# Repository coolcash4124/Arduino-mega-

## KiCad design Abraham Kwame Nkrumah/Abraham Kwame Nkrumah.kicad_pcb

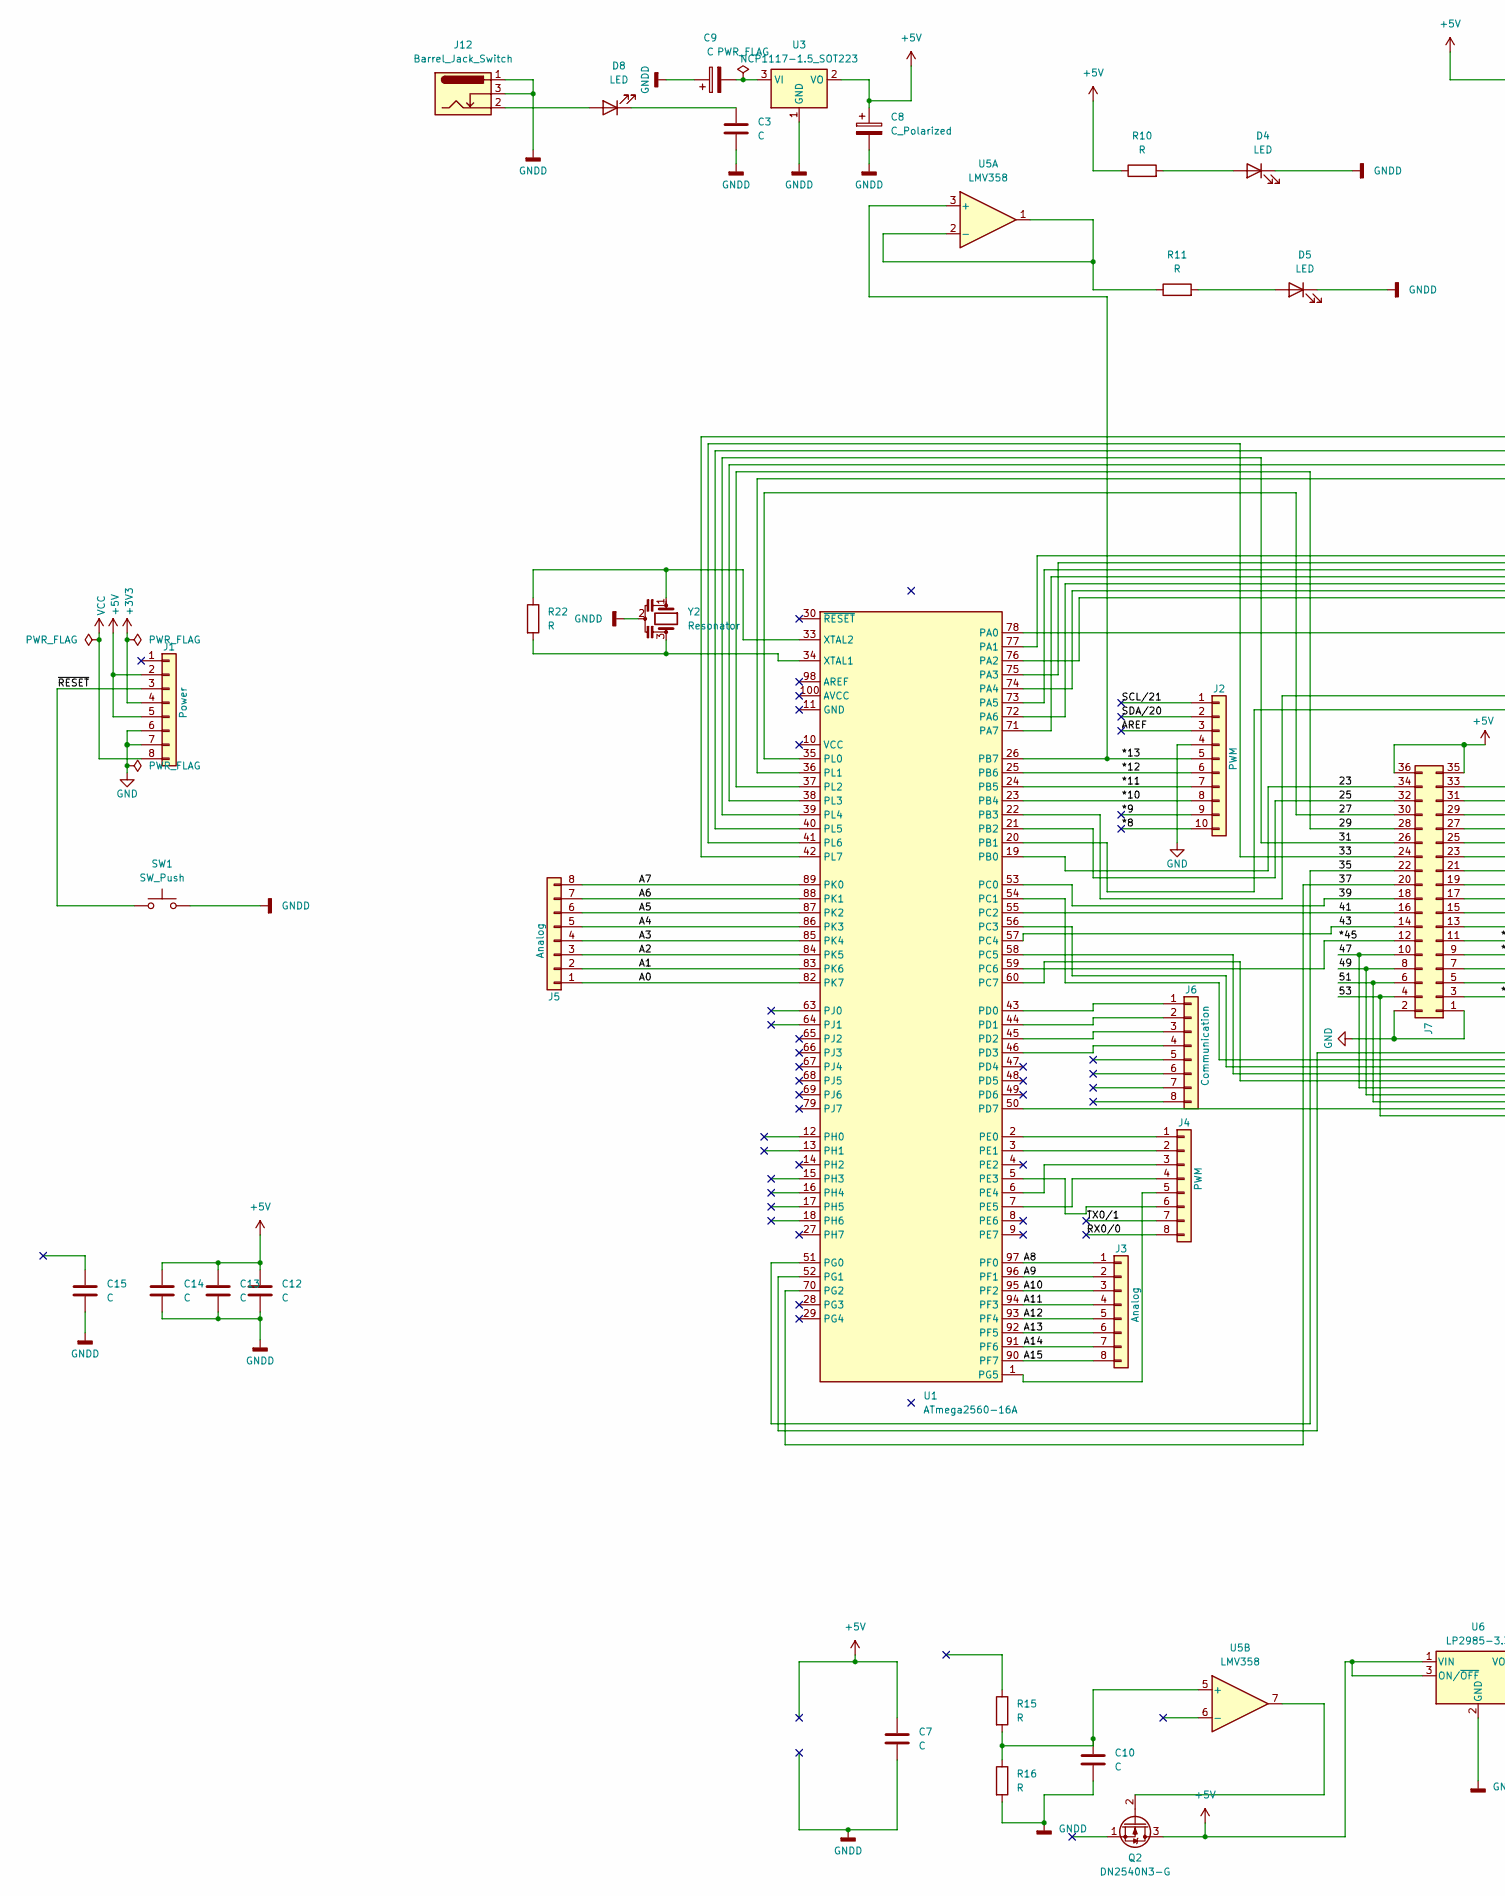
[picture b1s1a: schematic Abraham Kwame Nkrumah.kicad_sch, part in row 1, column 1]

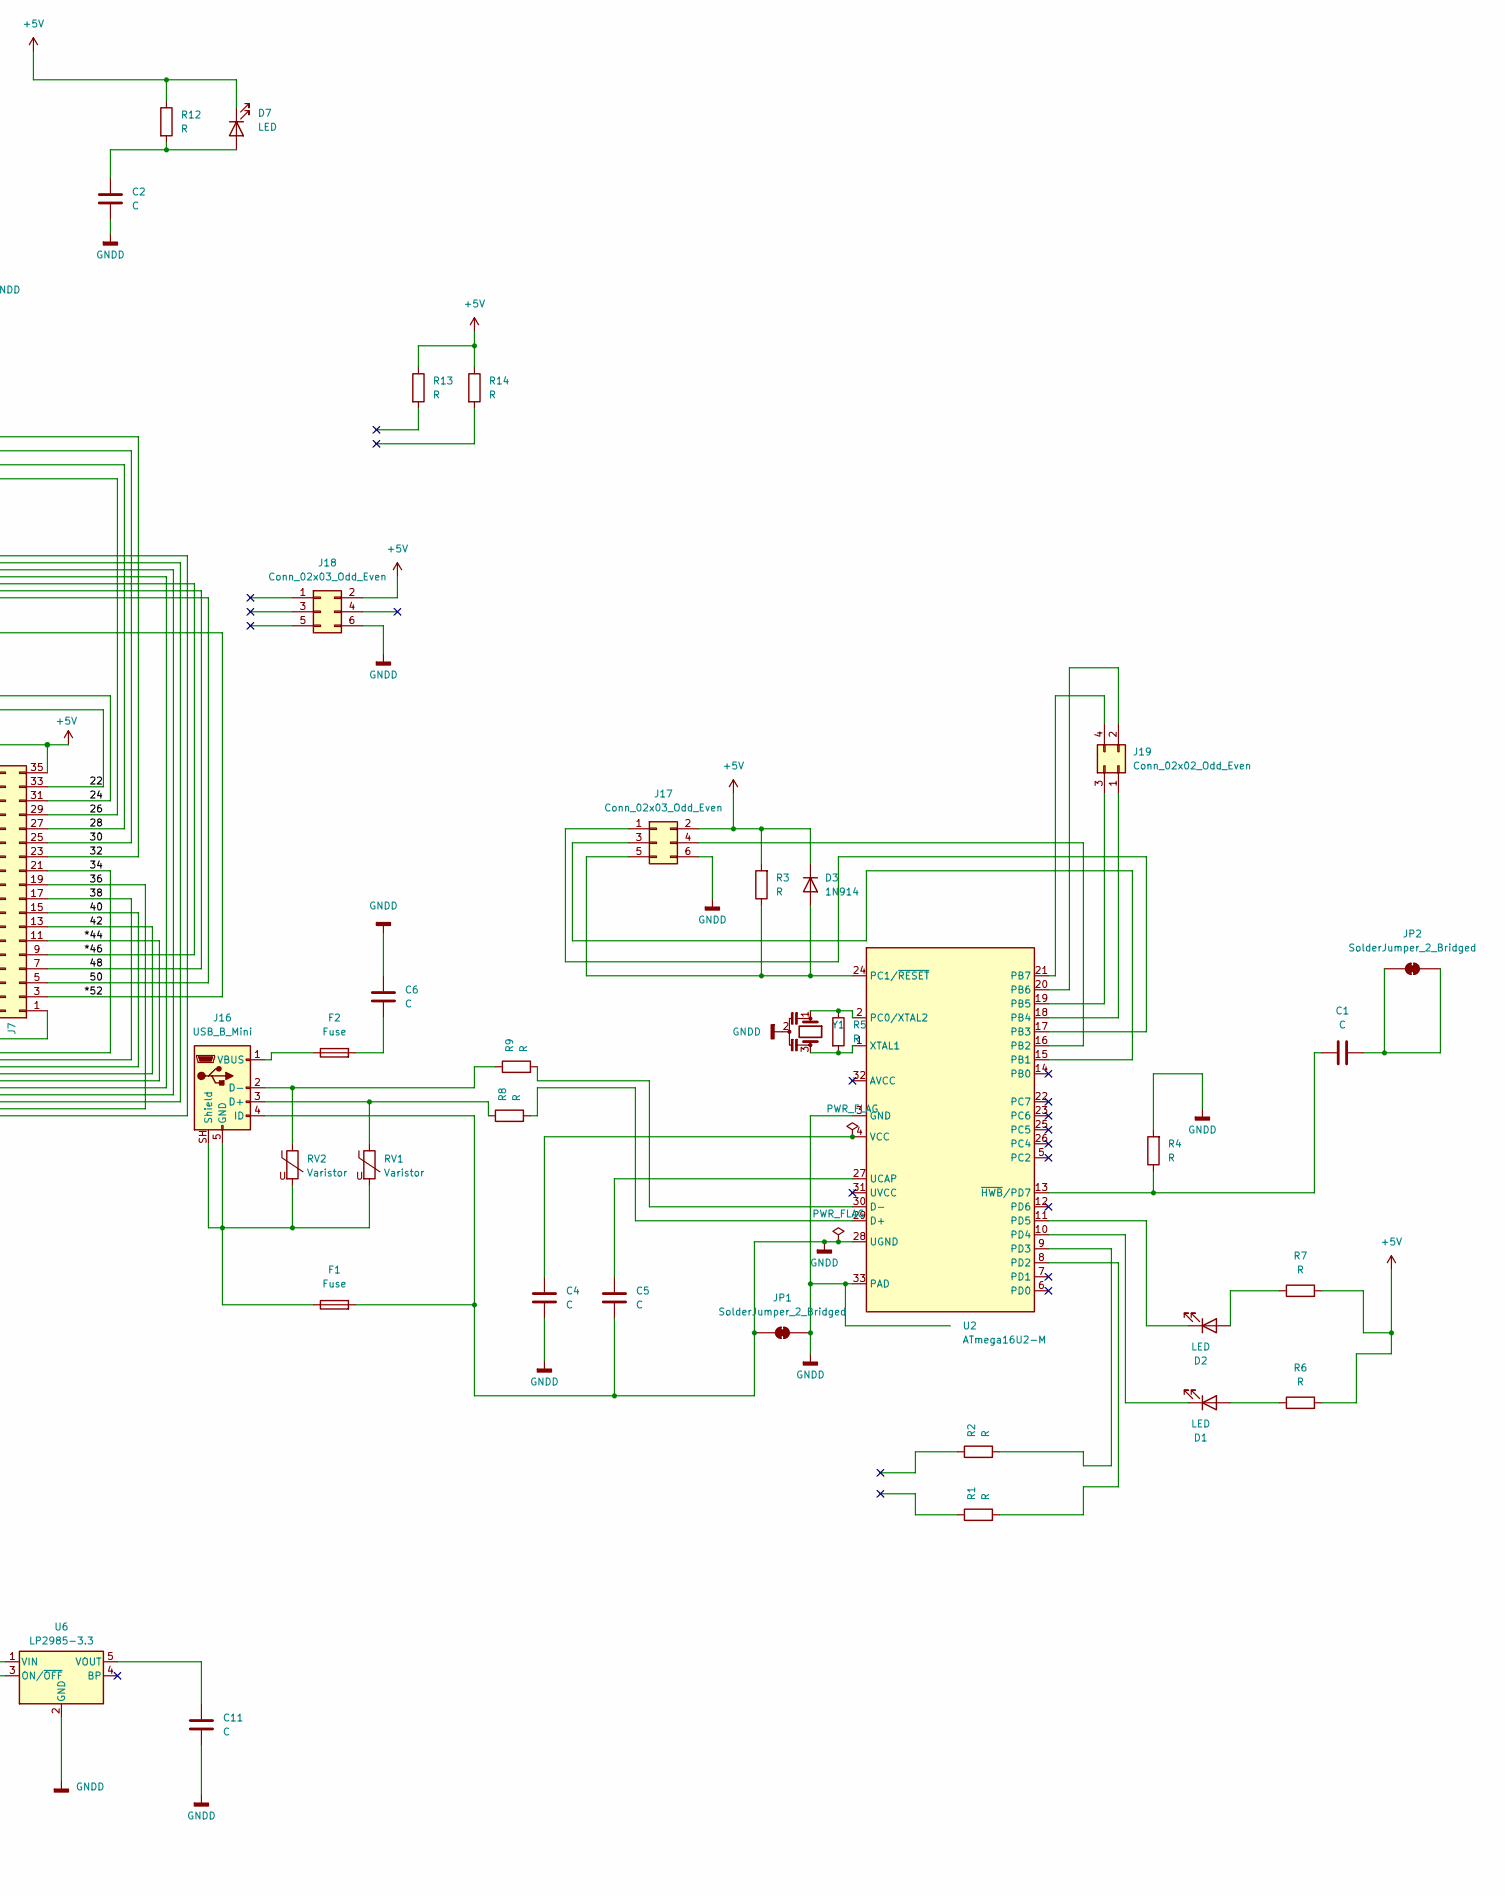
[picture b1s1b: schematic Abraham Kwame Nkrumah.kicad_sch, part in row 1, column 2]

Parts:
C1, C2, C3, C4, C5, C6, C11, C12, C13, C14, C15: C; C_0201_0603Metric_Pad0.64x0.40mm_HandSolder
C7: C; R_0201_0603Metric_Pad0.64x0.40mm_HandSolder
C8: C_Polarized; CP_Elec_4x3
C9: C; CP_Elec_4x3
C10: C; C_Disc_D3.0mm_W2.0mm_P2.50mm
D1, D2: LED; LED_0402_1005Metric
D3: 1N914; Diode_Bridge_DIP-4_W5.08mm_P2.54mm
D4, D5, D7, D8: LED; LED_0201_0603Metric
F1, F2: Fuse; Fuse_0603_1608Metric
J1: Power; PinSocket_1x08_P2.54mm_Vertical
J2: PWM; PinSocket_1x10_P2.54mm_Vertical
J3, J5: Analog; PinSocket_1x08_P2.54mm_Vertical
J4: PWM; PinSocket_1x08_P2.54mm_Vertical
J6: Communication; PinSocket_1x08_P2.54mm_Vertical
J7: Digital; PinSocket_2x18_P2.54mm_Vertical
J12: Barrel_Jack_Switch; BarrelJack_GCT_DCJ200-10-A_Horizontal
J16: USB_B_Mini; USB_B_Lumberg_2411_02_Horizontal
J17, J18: Conn_02x03_Odd_Even; PinSocket_2x03_P1.27mm_Vertical
J19: Conn_02x02_Odd_Even; Samtec_HLE-102-02-xxx-DV-BE-LC_2x02_P2.54mm_Horizontal
JP1, JP2: SolderJumper_2_Bridged; SolderJumper-2_P1.3mm_Bridged_RoundedPad1.0x1.5mm
Q2: DN2540N3-G; TO-92Flat
R1, R2, R3, R4, R5, R6, R7, R8, R9, R10, R13, R14, R15, R16, R22: R; R_0201_0603Metric_Pad0.64x0.40mm_HandSolder
R11: R; R_01005_0402Metric_Pad0.57x0.30mm_HandSolder
R12: R; R_0201_0603Metric
RV1: Varistor; RV_Disc_D12mm_W4mm_P7.5mm
RV2: Varistor; RV_Disc_D7mm_W3.5mm_P5mm
SW1: SW_Push; SW_PUSH_6mm_H5mm
U1: ATmega2560-16A; TQFP-100_14x14mm_P0.5mm
U2: ATmega16U2-M; QFN-32-1EP_5x5mm_P0.5mm_EP3.45x3.45mm
U3: NCP1117-1.5_SOT223; SOT-223-3_TabPin2
U5: LMV358; VSSOP-8_3x3mm_P0.65mm
U6: LP2985-3.3; SOT-23-5
Y1: Resonator; Resonator_Murata_DSS6-3Pin_W7.0mm_H2.5mm
Y2: Resonator; Resonator_Murata_CSTLSxxxG-3Pin_W8.0mm_H3.0mm

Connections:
+3V3: J1.4
+5V: C7.1, C8.1, C12.1, C13.1, C14.1, D3.1 (K), D7.1 (K), J1.2, J1.5, J7.35, J7.36, J17.2, J18.2, Q2.3 (D), R3.2, R6.2, R7.2, R10.1, R12.1, R13.1, R14.1, U3.2 (VO), U6.1 (VIN), U6.3 (ON/~OFF)
/22: J7.33, U1.20 (PB1)
/23: J7.34, U1.19 (PB0)
/24: J7.31, U1.22 (PB3)
/25: J7.32, U1.21 (PB2)
/26: J7.29, U1.36 (PL1)
/27: J7.30, U1.35 (PL0)
/28: J7.27, U1.38 (PL3)
/29: J7.28, U1.37 (PL2)
/30: J7.25, U1.40 (PL5)
/31: J7.26, U1.39 (PL4)
/32: J7.23, U1.42 (PL7)
/33: J7.24, U1.41 (PL6)
/34: J7.21, U1.52 (PG1)
/35: J7.22, U1.51 (PG0)
/36: J7.19, U1.50 (PD7)
/37: J7.20, U1.70 (PG2)
/38: J7.17, U1.54 (PC1)
/39: J7.18, U1.53 (PC0)
/40: J7.15, U1.56 (PC3)
/41: J7.16, U1.55 (PC2)
/42: J7.13, U1.58 (PC5)
/43: J7.14, U1.57 (PC4)
/47: J7.10, U1.71 (PA7)
/48: J7.7, U1.74 (PA4)
/49: J7.8, U1.73 (PA5)
/50: J7.5, U1.76 (PA2)
/51: J7.6, U1.75 (PA3)
/53: J7.4, U1.77 (PA1)
/*8: J2.10
/*9: J2.9
/*10: J2.8, U1.23 (PB4)
/*11: J2.7, U1.24 (PB5)
/*12: J2.6, U1.25 (PB6)
/*13: J2.5, U1.26 (PB7), U5.3 (+)
/*44: J7.11, U1.60 (PC7)
/*45: J7.12, U1.59 (PC6)
/*46: J7.9, U1.72 (PA6)
/*52: J7.3, U1.78 (PA0)
/A0: J5.1, U1.82 (PK7)
/A1: J5.2, U1.83 (PK6)
/A2: J5.3, U1.84 (PK5)
/A3: J5.4, U1.85 (PK4)
/A4: J5.5, U1.86 (PK3)
/A5: J5.6, U1.87 (PK2)
/A6: J5.7, U1.88 (PK1)
/A7: J5.8, U1.89 (PK0)
/A8: J3.1, U1.97 (PF0)
/A9: J3.2, U1.96 (PF1)
/A10: J3.3, U1.95 (PF2)
/A11: J3.4, U1.94 (PF3)
/A12: J3.5, U1.93 (PF4)
/A13: J3.6, U1.92 (PF5)
/A14: J3.7, U1.91 (PF6)
/A15: J3.8, U1.90 (PF7)
/AREF: J2.3
/RX0/0: J4.8
/SCL/21: J2.1
/SDA/20: J2.2
/TX0/1: J4.7
/~RESET: J1.3, SW1.1
GND: J1.6, J1.7, J2.4, J7.1, J7.2
GNDD: C2.2, C3.2, C4.2, C5.2, C6.1, C7.2, C8.2, C9.1, C10.2, C11.2, C12.2, C13.2, C14.2, C15.2, D4.1 (K), D5.1 (K), F1.2, J12.1, J12.3, J16.4 (ID), J17.6, J18.6, JP1.1 (A), JP1.2 (B), R4.2, R16.2, SW1.2, U2.3 (GND), U2.28 (UGND), U2.33 (GND), U3.1 (GND), U6.2 (GND), Y1.2, Y2.2
unnamed: C6.2, F2.2
unnamed: D1.2 (A), R6.1
unnamed: D1.1 (K), U2.10 (PD4)
unnamed: D2.2 (A), R7.1
unnamed: D2.1 (K), U2.11 (PD5)
unnamed: D3.2 (A), J17.5, R3.1, U2.24 (PC1/~RESET)
unnamed: D4.2 (A), R10.2
unnamed: D5.2 (A), R11.2
unnamed: C2.1, D7.2 (A), R12.2
unnamed: D8.2 (A), J12.2
unnamed: C3.1, D8.1 (K)
unnamed: J4.1, U1.2 (PE0)
unnamed: J4.2, U1.3 (PE1)
unnamed: J4.3, U1.6 (PE4)
unnamed: J4.4, U1.7 (PE5)
unnamed: J4.5, U1.1 (PG5)
unnamed: J4.6, U1.5 (PE3)
unnamed: J6.1, U1.43 (PD0)
unnamed: J6.2, U1.44 (PD1)
unnamed: J6.3, U1.45 (PD2)
unnamed: J6.4, U1.46 (PD3)
unnamed: J16.3 (D+), R8.1, RV1.1
unnamed: J16.2 (D-), R9.1, RV2.1
unnamed: F1.1, J16.5 (GND), J16.SH (Shield), RV1.2, RV2.2
unnamed: F2.1, J16.1 (VBUS)
unnamed: J17.1, U2.17 (PB3)
unnamed: J17.3, U2.15 (PB1)
unnamed: J17.4, U2.16 (PB2)
unnamed: J19.1, U2.18 (PB4)
unnamed: J19.2, U2.20 (PB6)
unnamed: J19.3, U2.19 (PB5)
unnamed: J19.4, U2.21 (PB7)
unnamed: C1.2, JP2.1 (A), JP2.2 (B)
unnamed: Q2.2 (G), U5.7
unnamed: R22.2, U1.34 (XTAL1), Y2.3
unnamed: R22.1, U1.33 (XTAL2), Y2.1
unnamed: R8.2, U2.29 (D+)
unnamed: R9.2, U2.30 (D-)
unnamed: R5.1, U2.2 (PC0/XTAL2), Y1.1
unnamed: R1.2, U2.8 (PD2)
unnamed: R2.2, U2.9 (PD3)
unnamed: C5.1, U2.27 (UCAP)
unnamed: C4.1, U2.4 (VCC)
unnamed: R5.2, U2.1 (XTAL1), Y1.3
unnamed: C1.1, R4.1, U2.13 (~HWB/PD7)
unnamed: C9.2, U3.3 (VI)
unnamed: R11.1, U5.1, U5.2 (-)
unnamed: C10.1, R15.2, R16.1, U5.5 (+)
unnamed: C11.1, U6.5 (VOUT)
VCC: J1.8

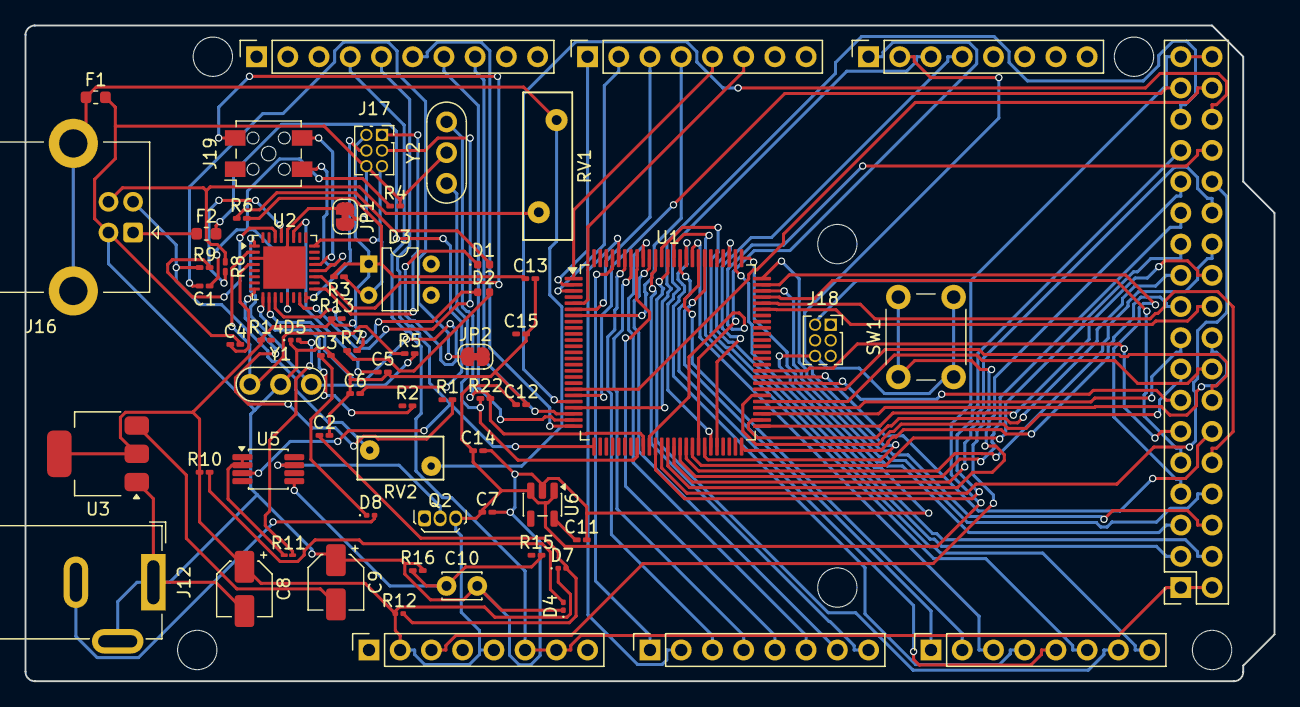
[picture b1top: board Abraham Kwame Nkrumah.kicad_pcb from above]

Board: 2 copper layers, 101.6 x 53.3 mm, 72 parts (0 on the bottom side), 105 nets.

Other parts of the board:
MH1, MH2, MH3, MH4, MH5, MH6: MountingHole_3.2mm
